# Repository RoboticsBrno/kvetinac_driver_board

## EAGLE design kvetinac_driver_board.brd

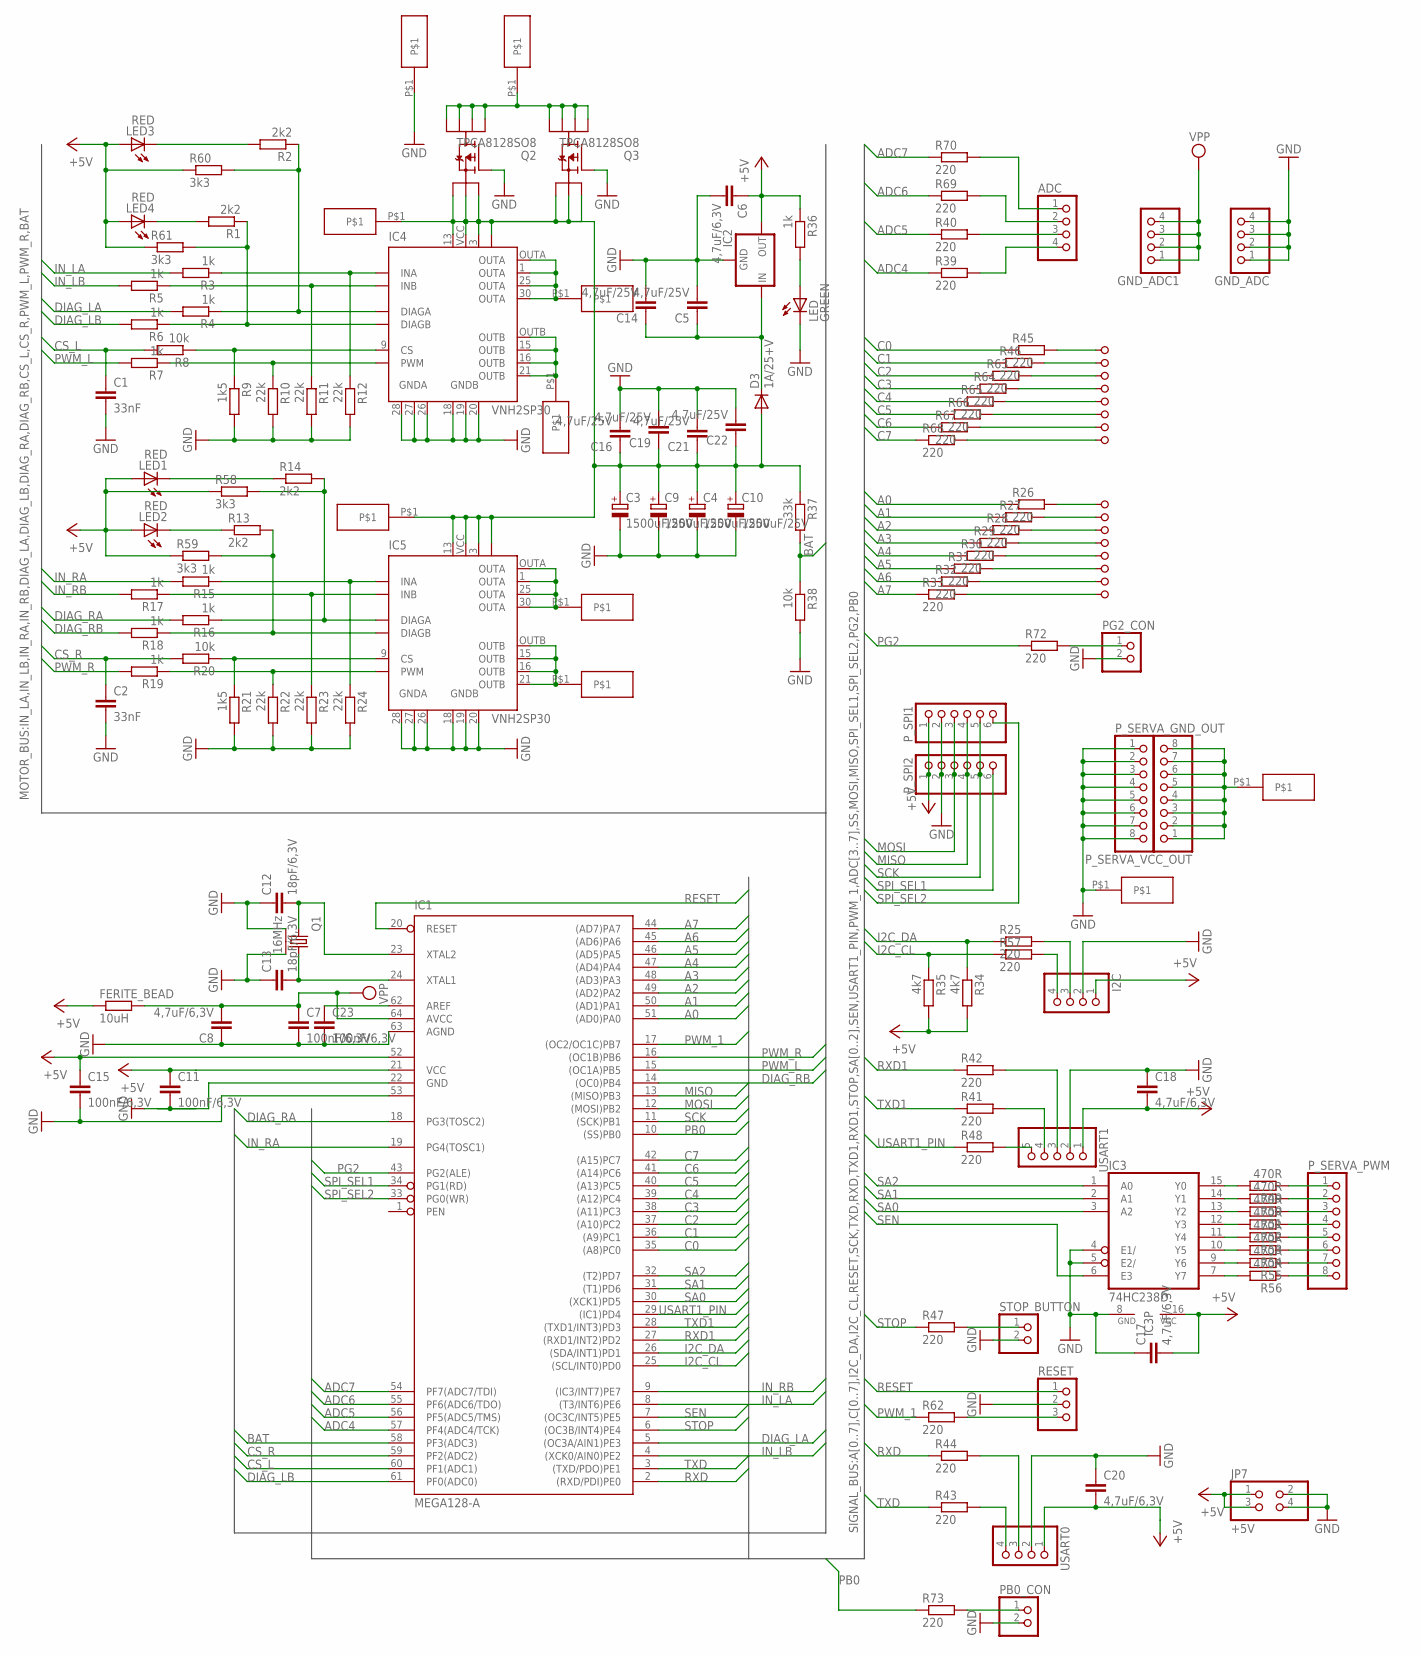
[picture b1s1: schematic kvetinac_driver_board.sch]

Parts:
0V: CABEL_SMD
ADC: PINHD-1X4; 1X04
C1, C2: 33nF; C0603
C3, C4, C9, C10: 1500uF/25V; E5-10,5
C5, C14, C16, C19, C21, C22: 4,7uF/25V; C0805
C6, C8, C17, C18, C20: 4,7uF/6,3V; C0805
C7, C11, C15, C23: 100nF/6,3V; C0306
C12, C13: 18pF/6,3V; C0603
D3: 1A/25+V; MINIMELF
FERITE_BEAD: 10uH; R0603
GND_ADC, GND_ADC1: PINHD-1X4; 1X04
I2C: PINHD-1X4; 1X04
IC1: MEGA128-A; TQFP64
IC2: 78XXS
IC3: 74HC238D; SO16
IC4, IC5: VNH2SP30; MULTIPOWERSO-30
J1, J2, J3, J4, J5, J6, J7, J8, J9, J10, J11, J12, J13, J14, J15, J16: PINHD-1X1SMD2.4MM; 1X01/SMD
JP7: +5V; 2X02
LED: GREEN; CHIPLED_0805
LED1, LED2, LED3, LED4: RED; CHIPLED_0805
OUTA_1, OUTA_2: CABEL_SMDCABEL_SMD_6.5*6MM; CABEL_SMD_6.5*6MM
OUTB_1, OUTB_2: CABEL_SMDCABEL_SMD_6.5*6MM; CABEL_SMD_6.5*6MM
PB0_CON: PINHD-1X2; 1X02
PG2_CON: PINHD-1X2; 1X02
P_SERVA_GND_OUT: PINHD-1X8; 1X08
P_SERVA_PWM: PINHD-1X8; 1X08
P_SERVA_VCC_OUT: PINHD-1X8; 1X08
P_SPI1, P_SPI2: PINHD-1X6; 1X06
Q1: 16MHz; ABM8
Q2, Q3: TPCA8128SO8; SO08-IRF
R1, R2, R13, R14: 2k2; R0603
R3, R4, R5, R6, R7, R15, R16, R17, R18, R19, R36: 1k; R0603
R8, R20, R38: 10k; R0603
R9, R21: 1k5; R0603
R10, R11, R12, R22, R23, R24: 22k; R0603
R25, R26, R27, R28, R29, R30, R31, R32, R33, R39, R40, R41, R42, R43, R44, R45, R46, R47, R48, R57, R62, R63, R64, R65, R66, R67, R68, R69, R70, R72, R73: 220; R0603
R34, R35: 4k7; R0603
R37: 33k; R0603
R49, R50, R51, R52, R53, R54, R55, R56: 470R; R0603
R58, R59, R60, R61: 3k3; R0603
RESET: PINHD-1X3; 1X03
STOP_BUTTON: PINHD-1X2; 1X02
USART0: PINHD-1X4; 1X04
USART1: PINHD-1X5; 1X05
VCC: CABEL_SMD
VCC1, VCC2: CABEL_SMD0.2*0.15; CABEL_SMD_0.25*0.15
VCCA: CABEL_SMDCABEL_SMD_12*6MM; CABEL_SMD_12*6MM
VCCB: CABEL_SMDCABEL_SMD_12*6MM; CABEL_SMD_12*6MM

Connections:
+5V: C6.1, C11.1, C15.1, C17.2, C18.2, C20.2, FERITE_BEAD.1, I2C.1, IC1.21 (VCC), IC1.52 (VCC1), IC2.OUT, IC3.16 (VCC), JP7.1, JP7.3, LED1.A, LED2.A, LED3.A, LED4.A, P_SPI1.1, P_SPI2.1, R34.2, R35.2, R36.1, R58.1, R59.1, R60.1, R61.1, USART0.1, USART1.1
A0: IC1.51 ((AD0)PA0), R26.1
A1: IC1.50 ((AD1)PA1), R27.1
A2: IC1.49 ((AD2)PA2), R28.1
A3: IC1.48 ((AD3)PA3), R29.1
A4: IC1.47 ((AD4)PA4), R30.1
A5: IC1.46 ((AD5)PA5), R31.1
A6: IC1.45 ((AD6)PA6), R32.1
A7: IC1.44 ((AD7)PA7), R33.1
ADC4: IC1.57 (PF4(ADC4/TCK)), R39.1
ADC5: IC1.56 (PF5(ADC5/TMS)), R40.1
ADC6: IC1.55 (PF6(ADC6/TDO)), R69.1
ADC7: IC1.54 (PF7(ADC7/TDI)), R70.1
AREF: C23.1, IC1.62 (AREF)
BAT: IC1.58 (PF3(ADC3)), R37.2, R38.1
C0: IC1.35 ((A8)PC0), R45.1
C1: IC1.36 ((A9)PC1), R46.1
C2: IC1.37 ((A10)PC2), R63.1
C3: IC1.38 ((A11)PC3), R64.1
C4: IC1.39 ((A12)PC4), R65.1
C5: IC1.40 ((A13)PC5), R66.1
C6: IC1.41 ((A14)PC6), R67.1
C7: IC1.42 ((A15)PC7), R68.1
CS_L: C1.1, IC1.60 (PF1(ADC1)), R8.2
CS_R: C2.1, IC1.59 (PF2(ADC2)), R20.2
DIAG_LA: IC1.5 ((OC3A/AIN1)PE3), R4.2
DIAG_LB: IC1.61 (PF0(ADC0)), R6.2
DIAG_RA: IC1.18 (PG3(TOSC2)), R16.2
DIAG_RB: IC1.14 ((OC0)PB4), R18.2
GND: 0V.P$1, C1.2, C2.2, C3.-, C4.-, C5.2, C6.2, C7.2, C8.1, C9.-, C10.-, C11.2, C12.1, C13.1, C14.2, C15.2, C16.2, C17.1, C18.1, C19.2, C20.1, C21.2, C22.2, C23.2, GND_ADC.1, GND_ADC.2, GND_ADC.3, GND_ADC.4, I2C.2, IC1.22 (GND), IC1.53 (GND1), IC1.63 (AGND), IC2.GND, IC3.4 (E1/), IC3.5 (E2/), IC3.8 (GND), IC4.18 (GNDB), IC4.19 (GNDB), IC4.20 (GNDB), IC4.26 (GNDA), IC4.27 (GNDA), IC4.28 (GNDA), IC5.18 (GNDB), IC5.19 (GNDB), IC5.20 (GNDB), IC5.26 (GNDA), IC5.27 (GNDA), IC5.28 (GNDA), JP7.2, JP7.4, LED.C, PB0_CON.2, PG2_CON.2, P_SERVA_GND_OUT.1, P_SERVA_GND_OUT.2, P_SERVA_GND_OUT.3, P_SERVA_GND_OUT.4, P_SERVA_GND_OUT.5, P_SERVA_GND_OUT.6, P_SERVA_GND_OUT.7, P_SERVA_GND_OUT.8, P_SPI1.2, P_SPI2.2, Q1.GND$1, Q1.GND$2, Q2.4 (G), Q3.4 (G), R9.2, R10.2, R11.2, R12.2, R21.2, R22.2, R23.2, R24.2, R38.2, RESET.2, STOP_BUTTON.2, USART0.2, USART1.2, VCC2.P$1
I2C_CL: IC1.25 ((SCL/INT0)PD0), R35.1, R57.1
I2C_DA: IC1.26 ((SDA/INT1)PD1), R25.1, R34.1
IN_LA: IC1.8 ((T3/INT6)PE6), R3.2
IN_LB: IC1.4 ((XCK0/AIN0)PE2), R5.2
IN_RA: IC1.19 (PG4(TOSC1)), R15.2
IN_RB: IC1.9 ((IC3/INT7)PE7), R17.2
MISO: IC1.13 ((MISO)PB3), P_SPI1.4, P_SPI2.4
MOSI: IC1.12 ((MOSI)PB2), P_SPI1.3, P_SPI2.3
unnamed: IC4.5 (INA), R3.1, R12.1
unnamed: IC5.10 (DIAGB), R13.2, R18.1, R59.2
unnamed: IC4.11 (INB), R5.1, R11.1
unnamed: IC5.6 (DIAGA), R14.2, R16.1, R58.2
unnamed: IC4.8 (PWM), R7.1, R10.1
unnamed: IC4.9 (CS), R8.1, R9.1
unnamed: IC4.6 (DIAGA), R2.1, R4.1, R60.2
unnamed: C12.2, IC1.23 (XTAL2), Q1.Q$1 (1)
unnamed: C13.2, IC1.24 (XTAL1), Q1.Q$2 (2)
unnamed: IC5.5 (INA), R15.1, R24.1
unnamed: IC4.10 (DIAGB), R1.1, R6.1, R61.2
unnamed: IC5.11 (INB), R17.1, R23.1
unnamed: LED1.C, R14.1
unnamed: IC5.8 (PWM), R19.1, R22.1
unnamed: IC5.9 (CS), R20.1, R21.1
unnamed: PG2_CON.1, R72.2
unnamed: ADC.3, R40.2
unnamed: LED2.C, R13.1
unnamed: LED.A, R36.2
unnamed: J9.1, R26.2
unnamed: J10.1, R27.2
unnamed: J11.1, R28.2
unnamed: J12.1, R29.2
unnamed: J13.1, R30.2
unnamed: J14.1, R31.2
unnamed: J15.1, R32.2
unnamed: J16.1, R33.2
unnamed: R41.2, USART1.4
unnamed: R42.2, USART1.3
unnamed: R43.2, USART0.4
unnamed: R44.2, USART0.3
unnamed: ADC.4, R39.2
unnamed: R48.2, USART1.5
unnamed: R47.2, STOP_BUTTON.1
unnamed: LED3.C, R2.2
unnamed: LED4.C, R1.2
unnamed: IC3.15 (Y0), R49.2
unnamed: PB0_CON.1, R73.2
unnamed: IC3.14 (Y1), R50.2
unnamed: IC3.13 (Y2), R51.2
unnamed: IC3.12 (Y3), R52.2
unnamed: IC3.11 (Y4), R53.2
unnamed: IC3.10 (Y5), R54.2
unnamed: IC3.9 (Y6), R55.2
unnamed: IC3.7 (Y7), R56.2
unnamed: P_SERVA_PWM.8, R56.1
unnamed: P_SERVA_PWM.7, R55.1
unnamed: P_SERVA_PWM.6, R54.1
unnamed: P_SERVA_PWM.5, R53.1
unnamed: P_SERVA_PWM.4, R52.1
unnamed: P_SERVA_PWM.3, R51.1
unnamed: P_SERVA_PWM.2, R50.1
unnamed: P_SERVA_PWM.1, R49.1
unnamed: R62.2, RESET.3
unnamed: I2C.3, R25.2
unnamed: ADC.2, R69.2
unnamed: ADC.1, R70.2
unnamed: I2C.4, R57.2
unnamed: J1.1, R45.2
unnamed: Q2.5 (D0), Q2.6 (D1), Q2.7 (D2), Q2.8 (D3), Q3.5 (D0), Q3.6 (D1), Q3.7 (D2), Q3.8 (D3), VCC.P$1
unnamed: J2.1, R46.2
unnamed: J3.1, R63.2
unnamed: J4.1, R64.2
unnamed: J5.1, R65.2
unnamed: J6.1, R66.2
unnamed: J7.1, R67.2
unnamed: J8.1, R68.2
unnamed: C5.1, C14.1, D3.C, IC2.IN
OUTA_1: IC4.1 (OUTA), IC4.25 (OUTA), IC4.30 (OUTA), IC4.OUTA, OUTA_1.P$1
OUTA_2: IC5.1 (OUTA), IC5.25 (OUTA), IC5.30 (OUTA), IC5.OUTA, OUTA_2.P$1
OUTB_1: IC4.15 (OUTB), IC4.16 (OUTB), IC4.21 (OUTB), IC4.OUTB, OUTB_1.P$1
OUTB_2: IC5.15 (OUTB), IC5.16 (OUTB), IC5.21 (OUTB), IC5.OUTB, OUTB_2.P$1
PB0: IC1.10 ((SS)PB0), R73.1
PG2: IC1.43 (PG2(ALE)), R72.1
PWM_1: IC1.17 ((OC2/OC1C)PB7), R62.1
PWM_L: IC1.15 ((OC1A)PB5), R7.2
PWM_R: IC1.16 ((OC1B)PB6), R19.2
RESET: IC1.20 (RESET), RESET.1
RXD: IC1.2 ((RXD/PDI)PE0), R43.1
RXD1: IC1.27 ((RXD1/INT2)PD2), R42.1
SA0: IC1.30 ((XCK1)PD5), IC3.3 (A2)
SA1: IC1.31 ((T1)PD6), IC3.2 (A1)
SA2: IC1.32 ((T2)PD7), IC3.1 (A0)
SCK: IC1.11 ((SCK)PB1), P_SPI1.5, P_SPI2.5
SEN: IC1.7 ((OC3C/INT5)PE5), IC3.6 (E3)
SERVA_VCC: P_SERVA_VCC_OUT.1, P_SERVA_VCC_OUT.2, P_SERVA_VCC_OUT.3, P_SERVA_VCC_OUT.4, P_SERVA_VCC_OUT.5, P_SERVA_VCC_OUT.6, P_SERVA_VCC_OUT.7, P_SERVA_VCC_OUT.8, VCC1.P$1
SPI_SEL1: IC1.34 (PG1(RD)), P_SPI2.6
SPI_SEL2: IC1.33 (PG0(WR)), P_SPI1.6
STOP: IC1.6 ((OC3B/INT4)PE4), R47.1
TXD: IC1.3 ((TXD/PDO)PE1), R44.1
TXD1: IC1.28 ((TXD1/INT3)PD3), R41.1
USART1_PIN: IC1.29 ((IC1)PD4), R48.1
VCC: C3.+, C4.+, C9.+, C10.+, C16.1, C19.1, C21.1, C22.1, D3.A, IC4.3 (VCC), IC4.13 (VCC), IC4.23 (VCC), IC4.VCC, IC5.3 (VCC), IC5.13 (VCC), IC5.23 (VCC), IC5.VCC, Q2.1 (S0), Q2.2 (S1), Q2.3 (S2), Q3.1 (S0), Q3.2 (S1), Q3.3 (S2), R37.1, VCCA.P$1, VCCB.P$1
VPP: C7.1, C8.2, FERITE_BEAD.2, GND_ADC1.1, GND_ADC1.2, GND_ADC1.3, GND_ADC1.4, IC1.64 (AVCC)

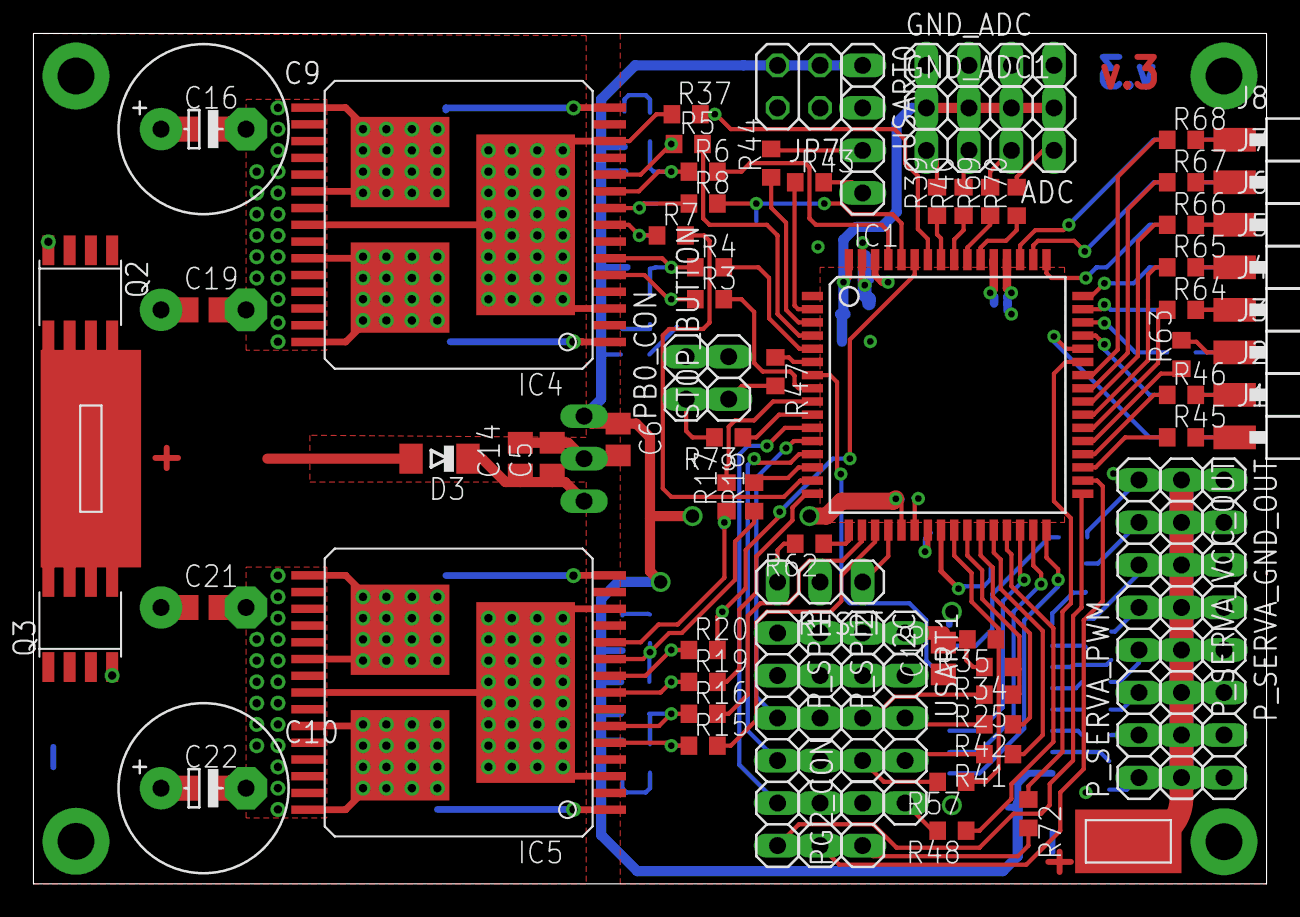
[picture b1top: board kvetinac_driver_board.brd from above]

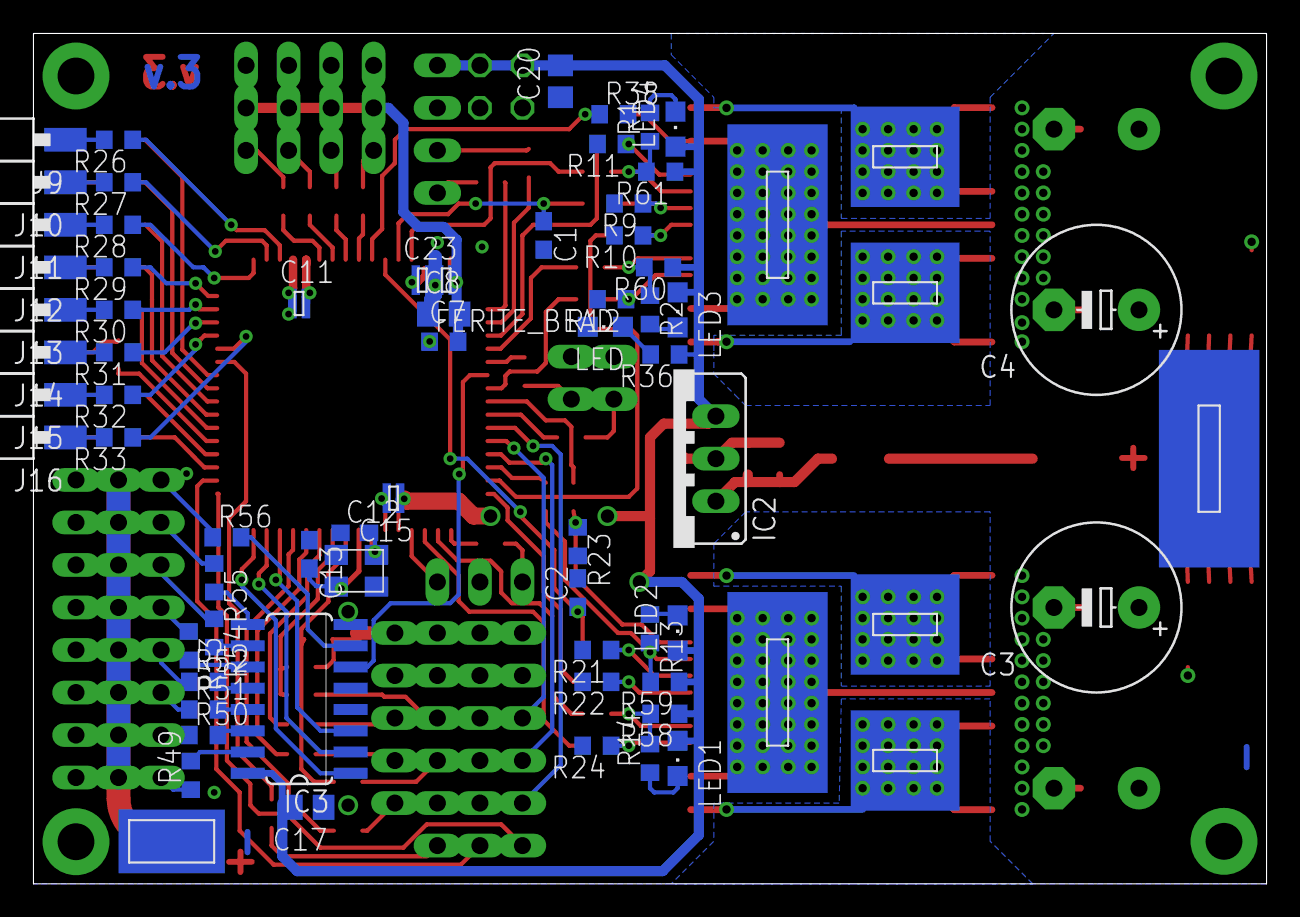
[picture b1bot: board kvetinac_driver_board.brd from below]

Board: 2 copper layers, 73.7 x 50.8 mm, 152 parts (72 on the bottom side), 132 nets.

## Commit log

2010-11-17 Initial commit.
2011-01-09 Pridany 4 piny s 5V, pridan 1 pin k USART1 pro novy bluetooth a max485 a vyveden jeden pin s PWM.
2011-01-09 add 2x 5V power connector
2011-02-15 add version
2011-08-24 Reedit schema.
2011-09-27 Kompletne predelana deska - momentalne rozpracovany. Vyreseno vykonove napajeni, stabilizace a napajeni cipu. Pridan popis projektu - DESCRIPTION (vse dulezite napsano tam).
2011-10-02 Provedeny zmeny: - vsechny rezistory predelany z 0805 na 0603 - napajeci kondenzatory 0306 - predchystany konektory pro USART a I2C
2011-11-09 Preroutovana na 80%. Potreba dodelat.
2011-11-12 Doroutovano (100%). V pripominkovym rizeni (potreba prekontrolovat).
2011-11-13 Vedle piheadu STOP_BUTTON A PWM1 pridany pinheady pripojene na GND. (Kubova pripominka)
2012-01-13 Upravy podle Kuby Straita.
    Opraveny polygony kv?li zkratu (zmenen Rank u polygonu GND).
    Predelana pozice pinheadu SCK.
    Prepsan description.
2012-01-21 Upravena soucastka VNH2SP30 (predelano schema i package).
    Upravena deska, vymenena soucastka ve schametu i v desce.
    Prohlednout description (zajimave poznamky)!
2012-01-21 Provedeny zmeny na desce i ve schematu.
    Otoceny vsechny ledky na stranu top (na stranu kde jsou pinheady) a pin SS pripojen na P_SPI0.
2012-01-22 predelany konektor porta a potrc prehozene ovladaci linky k driverum
2012-01-22 pridana knihovna
2012-01-24 pokracovani v routovani
2012-02-05 ve vystavbe
2012-02-05 skoro hotovo zbyvaji pajeci plosky pro draty
2012-02-08 finalni upravy pro vyrobu
2012-02-08 do vyroby v.1
2012-02-09 verze pro vyrobu, pridan soubor .dru
2012-03-05 pridany hodnoty jednotlivych soucastek (probehla rychla kontrola schema)
2012-04-06 Upravena deska a schema - pridany a prepsany hodnoty soucastek
    Upraveno deskription.
2012-06-12 ochrana proti prepolovani presunuta na VCC pridano pajeci ploska pro napajeni serv (bez ochrany proti prepolovani) prohozeny SPI_SEL1 a SPI_SEL2 pridany konektory na PB0 a PG2 verze v.2
2012-07-15 prohozene DIAG_LB a CS_L kvuli lepsi sw citelnosti
2012-07-16 AREF pripojen pres 100nF ke GND, misto k AVCC - umoznuje pouzit interni 2.56V referenci
2012-10-18 Upraven popis soucastek (Led1 az Led4 a kondenzatory C17, C18, C20).
2013-01-14 Nov? verze: Upraveny plosky pod drivery VNH2SP30. Pridany vie pod drivery VNH2SP30 - kvuli umozneni pripajeni z druhe strany.
    Upraven DESCRIPTION:
    Pridany INSTRUKCE PRO VYROBU a pro PRVNI OZIVENI DESKY.
    Popsany vsechny veci kolem desky a jeji vyroby.
    VSICHNI POVINNE PROCIST!!!
2013-02-17 Rozt?hnuty polygony pod driverama (v?vod A a B) - v.3
    Dohromady s p?edchoz?m commitem (prokovy pod driverama - plo?ka GND) tvo?? novou verzi 3.
2016-06-16 Aktualizov?n DESCRIPTION
